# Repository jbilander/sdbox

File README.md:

# SDBox for Amiga

***
This version `v1` is superseded by the new `SDBox-v2` here: https://github.com/jbilander/SDBox-v2

There is also a SDBox Mini available here: https://github.com/jbilander/SDBox-Mini
***

### A parallel to sd-card project for the Amiga

This code uses the code from the amiga-par-to-spi-adapter https://github.com/niklasekstrom/amiga-par-to-spi-adapter written by Niklas Ekström. KiCad design, Schematics and files for DesignSpark Mechanical v4 is made by me. Design of the 3d-printable sdbox case is made by me and Tobias Niva (niva3d, http://www.niva3d.com/). It is a collaborative work done by us three, Enjoy!

***

***

What is the sdbox for Amiga? 

It is a small device that you can plug into your Amiga's parallel port and get access to a sd-card formatted with e.g. a windows FAT file system. It uses an Arduino Nano V3 and a common cheap MicroSD Card Adapter that has a voltage level shifter on board. These small devices are soldered onto a small PCB together with a male d-sub db25 connector that fits into the Amiga parallel port (The A1000 needs a proper gender changer, be aware). The device must be powered externally either through the usb-connector on the Nano or via the separate barrel jack connector on the main PCB. A power supply with 1A DC capacity should suffice. `5V` via USB or `7-12V` via the barrel jack power connector that goes to the VIN of the Nano V3. The driver should be AmigaOS system friendly but takes exclusive access over the parallel port so don't expect to run other things on this port together with the sdbox with some kind of breakout cable. It should work from 1.3 and upwards, verified working on 1.3, 3.1 and 3.1.4 so far.

The schematics, BOM, kicad drawings and the 3d-printable case source and stl files can all be found in the hardware folder.

PCBs can be order directly via link below or you can send the gerbers zip (or generate gerbers yourself) and send them to your favorite boardhouse.

https://aisler.net/p/YVXJBQHM

***
Ok enough talk!, show us some videos:
<br />

Copying from Amiga to sd-card<br />
https://i.imgur.com/um15pal.mp4

Copying from sd-card to the Amiga (cpu fastrom activated, KS ROM loaded into Fast RAM)<br />
https://i.imgur.com/G6VRPpx.mp4

Copying from sd-card to the Amiga  (without fastrom activated) <br />
https://i.imgur.com/ADebdlJ.mp4

***

***

<br />

More rendered pictures and concepts by `niva3d` under the `images/_renders` directory, made in Blender, check it out!

***

### 3d-printing

Check the README in the `hardware/DSM` folder

***

### Howto build the spisd.device driver

Check the README in the sd folder.

For the lazy: Binaries available now in a zip file under the `release` tab above.

***

### Caveats

One little caveat to keep in mind is that we do no CRC-verification of data being copied so please verify your files afterwards manually if you are going to copy important files over this way like taking a backup or something. Another caveat is that not all sd-cards might work with the sdbox so aim for a cheap 4/8 GB card and format it with a smaller partition `below 4GB` with FAT is a good starting point. If you see an error message saying `bad number` when trying to mount `SD0` it may be an indication that your particular sd-card simply doesn't work with the sdbox for some reason.

Everything done here is provide `as is`, don't blame us if your Amiga CIAs dies or your files get corrupted using the sdbox. I don't think it will happen though. Be careful though when plugging the sdbox in or out of the Amiga, always do that with the Amiga turned off.

    Some advice from Tom Handley / 18 April 93 (taken from pario on Aminet)

    NEVER connect, disconnect, or switch, parallel port lines with the power on!  
    ALWAYS shut the power off first!  In most cases, you should use the following sequence:

       Power up:   - Turn on your Amiga
                   - Turn on the external device

       Power down: - Turn off the external device
                   - Turn off your Amiga
                   
    If you have been switching devices with the power on you have been lucky...
    Not following the above precaution, and static electricity, are the two main
    causes of user-induced 8520 failures.
***

The sequence I use when powering the sdbox via USB is this:

* Plug the micro sd-card into the MicroSD card slot of the sdbox
* With the Amiga turned off plug the sdbox into the Amiga 
* Connect the +5V USB power cable into the sdbox, the two LEDs will light up with a steady shine. Don't worry that the activity LED light turns on, it's on when the SEL/CS line goes low (Zero). It will turn off as soon as the Amiga is turned on.
* Turn on the Amiga
* In wb mount the card
* When done, turn off the Amiga, the sdbox Activity LED will light up again as a reminder to unplug the USB power cable
* Unplug the sdbox from the Amiga if you want to remove it.

This has worked without any issues for me.

Hopefully powering via the barrel jack and using U3 chip (Solid State Relay) will work and automatically handle the Power cycling following the Amiga's on/off.

__UPDATE: Powering via the barrel jack is now verified and working.__ see last section in this readme

***

### Kudos

Many thanks to Mike Stirling for writing the original k1208-drivers and making them open source, we built further on his code. It was a good starting point. Thanks Mike and kipper2k and others involved in k1208.

***

### Performance 

What about performance you may ask? 

Well, Niklas managed to write the drivers with some real clever assembler to make it go at 2E-speed (theoretical 350 KB/s, IRL around 225-280 KB/s) if you have some kind of Accelerator installed in your A500. 
Copying a 23 MB file from the SD-card to the compact flash in the HC508 took 98 seconds, giving a throughput of 225 KB/s. We think this is a good result given the fact of the slow clocking of the CIAs (E-clock). It will also work with a standard 68k CPU at 7 MHz although slower.

With my TF534 and 3.1 rom loaded into Fast RAM via the command `cpu fastrom` (requires a MMU) I get 280 KB/s in SysInfo, and without fastrom 250 KB/s. It is a little slower copying to the Amiga than from the Amiga.

Speed definition of 2E here: <br />
https://lallafa.de/blog/2015/09/amiga-parallel-port-how-fast-can-you-go/

***

### Howto build the sdbox

Start with removing the angled pins from the MicroSD Card Adapter and replace with straight pins like shown on pictures below:

***

Now we start soldering on the surface mount parts, the passives, also known as the birdseed :) Start with Q1 and Q2, they are tiny so you probably need some sort of magnification. I use a lamp with a built-in magnifier glass, it works well, I do not have a microscope. Use a fine tip with your solder iron...

***

***

Now with the surface mount stuff done we do the through-hole stuff, solder on two cut-down pins as leg support for the MicroSD Card Adapter, the adapter will rest on these and make it in level and the same height as the Nano.

***

***

Now, with this type of connector the metal plate comes loose when you unscrew the connector nuts. We need to remove them because we don't want to remove them on the Amiga side. Use some super glue and a vise or similar to press them together a couple of minutes until the glue bites. Be quick if you use super glue! Then put the screws back while soldering, we want the metal pieces in there as a support taking some force off the pins when plugging the device in and out of the Amiga.

***

***

Now solder the MicroSD Card Adapter and the Nano down to the PCB as well.

***

***

Almost done!, time to put the LEDs in. To get the correct LED height for the sdbox 3d-printable case, I used a leftover trial print of the bottom part and drilled a hole through it to give me access to tack the LEDs down, with the iron, while holding the LEDs in place pressing on the legs gently. Cut the legs like in the picture below so that you can remove the pcb from the case and solder and trim them better afterwards. Job done!

***

***
### Update: Powering via the barrel jack

So I finally got parts to try out powering the device via the optional barrel jack. It seems to work just fine. I used a `9V DC 1A`, center pin positive, adapter.

Solder the barrel jack and the solid state relay (PVG612S) to the PCB. I made a small parallel extension adapter in order to let me easily measure the control current draw of the `PVG612S`.

***

***

Video clip below, as you can see powering of the sdbox is now controlled by the Amiga's on/off and you can just leave the sdbox always connected via the barrel jack. The control current draw for the solid state relay is around `9.7 mA` which is just below the `10 mA` max recommended draw from the Amigas parallel port pin 14. Great!

https://i.imgur.com/eSkcy3X.mp4

First checking the `9V` adapter and verifying it is indeed center pin positive and outputs around 9V. It shows around `9.3V`. The current draw I measured to around `9.7 mA` with the `330 Ohm` on R5 in series with the Amigas internal `47 Ohm`. Voltage input to `PVG612S` is around `1.2V`, perfect! The `5V` on the Nano V3 shows `5.03V`, Spot On!

***

***

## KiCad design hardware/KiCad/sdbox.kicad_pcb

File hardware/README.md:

## sdbox for Amiga

This is a PCB made in KiCad (5.1.2-1) for hooking up an Arduino Nano V3 with a micro-sd-card module to the Amiga parallel-port.

***

For 3d-printing the sdbox case, check the README in the DSM folder.

***

BOM, now verified!

Please note, you don't need to populate C1 if you're not going to use the barrel jack. R5 is only needed if U3 is populated.
***

PART  | Value | Description
----- | ----- | -------
U1    |       | Arduino Nano V3
U2    |       | Micro SD-Card Adapter (with onboard bidirectional level shifter)
U2    |Pin strip| 1 Pcs 2.54mm Single Row Male Pin Header Strip For mounting and connecting Micro SD-Card Adapter directly into base PCB. Cut out one with 6 pins and two with single pins. The current angled pins on module will be desoldered and removed.
U3    |PVG612S| Solid State Relay, 6-SMD (0,300", 7,62mm) Automatic power down with the Amiga (optional)
J1    |DB25   | DB25 Male MountingHoles 
J2    |5.5x2.1 mm | Barrel Jack Power Connector, center positive (optional)
C1    |100uF-220uF| 1210 ceramic decoupling capacitor for VIN, 16 VDC or at least above you voltage input 7-12V. Not needed if powering via USB.
R1    |4.7k Ohm| 1206 smd resistor (should give around 0.9mA when CS/SEL is high)
R2    |4.7k Ohm| 1206 smd resistor
R3    |120 Ohm| 1206 smd resistor (should give around 2.14V, 24 mA over D1)
R4    |120 Ohm| 1206 smd resistor (should give around 2.17V, 24 mA over D2)
R5    |330 Ohm| 1206 smd resistor (should give around 1.2V and 10 mA control current with the Amiga 47 Ohm in series from pin 14) Not needed if U3 not populated
D1    |LED 3mm| SD Activity LED, Diffused Orange / Amber, pitch 2.54 mm, 1.8V-2.3V, 20-30 mA, 605-610nm
D2    |LED 3mm| Power LED, Green Diffused T-1, pitch 2.54 mm, 25 mcd, 565 nm, 2.2 V, 25 mA
Q1    |BC847BW| Small Signal Transistor, NPN polarity, SOT-323
Q2    |BC847BW| Small Signal Transistor, NPN polarity, SOT-323
JP1   |Solder jumper| Enable this to reset Nano in conjunction with Ctrl-Amiga-Amiga
JP2   |Solder jumper| Enable this to use barrel jack connector without U3 chip

***

***

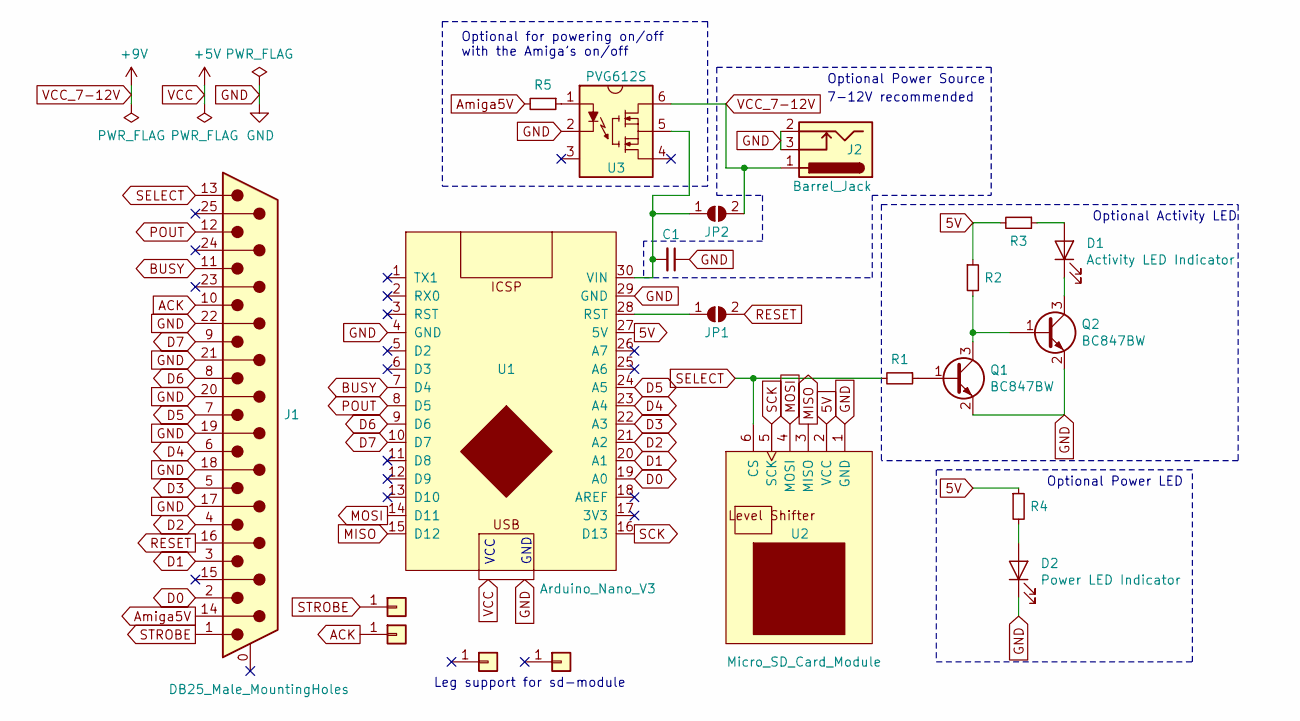
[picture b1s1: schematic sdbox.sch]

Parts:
C1: C_Small; C_1210_3225Metric_Pad1.42x2.65mm_HandSolder
D1: Activity LED Indicator; LED_D3.0mm
D2: Power LED Indicator; LED_D3.0mm
J1: DB25_Male_MountingHoles; DSUB-25_Male_Horizontal_P2.77x2.84mm_EdgePinOffset4.94mm_Ho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
J2: Barrel_Jack; BarrelJack_Horizontal
J3, J4: Conn_01x01; PinHeader_1x01_P2.54mm_Vertical
J5, J6: Conn_01x01; PinSocket_1x01_P2.54mm_Vertical
JP1, JP2: SolderJumper_Open; SolderJumper-2_P1.3mm_Open_Pad1.0x1.5mm
Q1, Q2: BC847BW; SOT-323_SC-70
R1, R2, R3, R4, R5: R_Small; R_1206_3216Metric_Pad1.42x1.75mm_HandSolder
U1: Arduino_Nano_V3; Arduino_Nano_V3_Schield
U2: Micro_SD_Card_Module; PinSocket_1x06_P2.54mm_Vertical
U3: PVG612S; SOIC254P978X443-6N

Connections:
5V: R2.1, R3.2, R4.1, U1.27 (5V), U2.2 (VCC)
ACK: J1.10, J4.1
Amiga5V: J1.14, R5.2
BUSY: J1.11, U1.7 (D4)
D0: J1.2, U1.19 (A0)
D1: J1.3, U1.20 (A1)
D2: J1.4, U1.21 (A2)
D3: J1.5, U1.22 (A3)
D4: J1.6, U1.23 (A4)
D5: J1.7, U1.24 (A5)
D6: J1.8, U1.9 (D6)
D7: J1.9, U1.10 (D7)
GND: C1.1, D2.1 (K), J1.17, J1.18, J1.19, J1.20, J1.21, J1.22, J2.2, J2.3, Q1.2 (E), Q2.2 (E), U1.4 (GND), U1.29 (GND), U2.1 (GND), U3.2
MISO: U1.15 (D12), U2.3 (MISO)
MOSI: U1.14 (D11), U2.4 (MOSI)
unnamed: C1.2, JP2.1 (A), U1.30 (VIN), U3.5
unnamed: D1.1 (K), Q2.3 (C)
unnamed: D1.2 (A), R3.1
unnamed: D2.2 (A), R4.2
unnamed: JP1.1 (A), U1.28 (RST)
unnamed: Q1.1 (B), R1.1
unnamed: Q1.3 (C), Q2.1 (B), R2.2
unnamed: R5.1, U3.1
POUT: J1.12, U1.8 (D5)
RESET: J1.16, JP1.2 (B)
SCK: U1.16 (D13), U2.5 (SCK)
SELECT: J1.13, R1.2, U2.6 (CS)
STROBE: J1.1, J3.1
VCC_7-12V: J2.1, JP2.2 (B), U3.6

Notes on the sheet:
Optional for powering on/off with the Amiga’s on/off
Optional Power Source
7-12V recommended
VCC
GND
Leg support for sd-module
Optional Activity LED
Optional Power LED

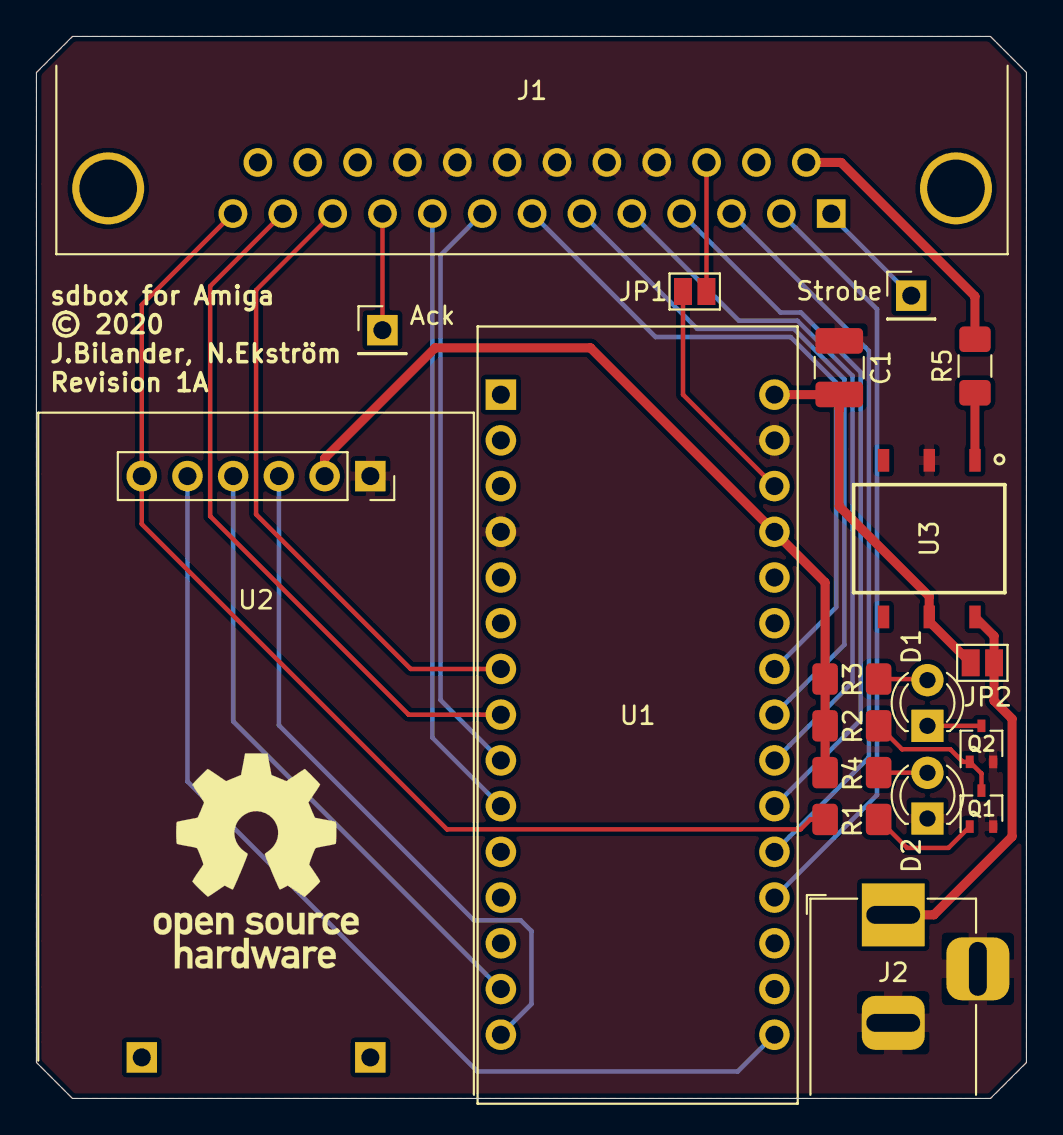
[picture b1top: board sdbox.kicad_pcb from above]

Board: 2 copper layers, 55.0 x 59.0 mm, 21 parts (0 on the bottom side), 29 nets.

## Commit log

2020-03-02 base skel
2020-03-02 edited gitignore file
2020-06-05 restructure of repo
2020-06-05 added source files
2020-06-05 added images
2020-06-05 changed to correct license GPLv3
2020-06-05 corrected driver name
2020-06-06 added niva3d render images
2020-06-06 added source files for 3d OBJ-format
2020-06-07 adapted to gcc-2.95 amigaos-cross-toolchain
2020-06-07 adapted to gcc-2.95.3 amigaos-cross-toolchain
2020-06-08 corrected id string
2020-06-08 added file
2020-06-08 Updated file
2020-06-13 Remove loading of unused libraries
    The libraries were not being used, and prevented the driver from loading
    on kickstart 1.3.
2020-06-16 edited file
2020-06-16 added files
2020-06-27 forgot to bump DevRevision = 3
2020-11-07 Update spi-par.c
    More elegant way to avoid blocking boot sequence if adaptor is not physically present.
2020-11-07 Update spi.h
    Including timer.h header file.
2020-11-08 Bump to DevRevision = 4
2020-12-08 fixed debugging now possible via kprintf
2020-12-09 Set default debug level = 3 (show all)
2021-03-13 updated gitignore
2021-03-13 add schematic pdf
2021-03-13 fixed symbol and footprint libs now included as project libs
2021-03-13 updated image
2021-03-13 added gerbers
2021-03-13 deleted sdbox.dcm

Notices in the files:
hardware/KiCad/sdbox.kicad_pcb:
© 2020
